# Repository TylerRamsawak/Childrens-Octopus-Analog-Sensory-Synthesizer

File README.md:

# Children's Octopus-themed Analog Sensory Synthesizer

<h3>Rendered 3D model of the PCB</h3>
<br>
<h3>Schematic of the synth and inputs</h3>

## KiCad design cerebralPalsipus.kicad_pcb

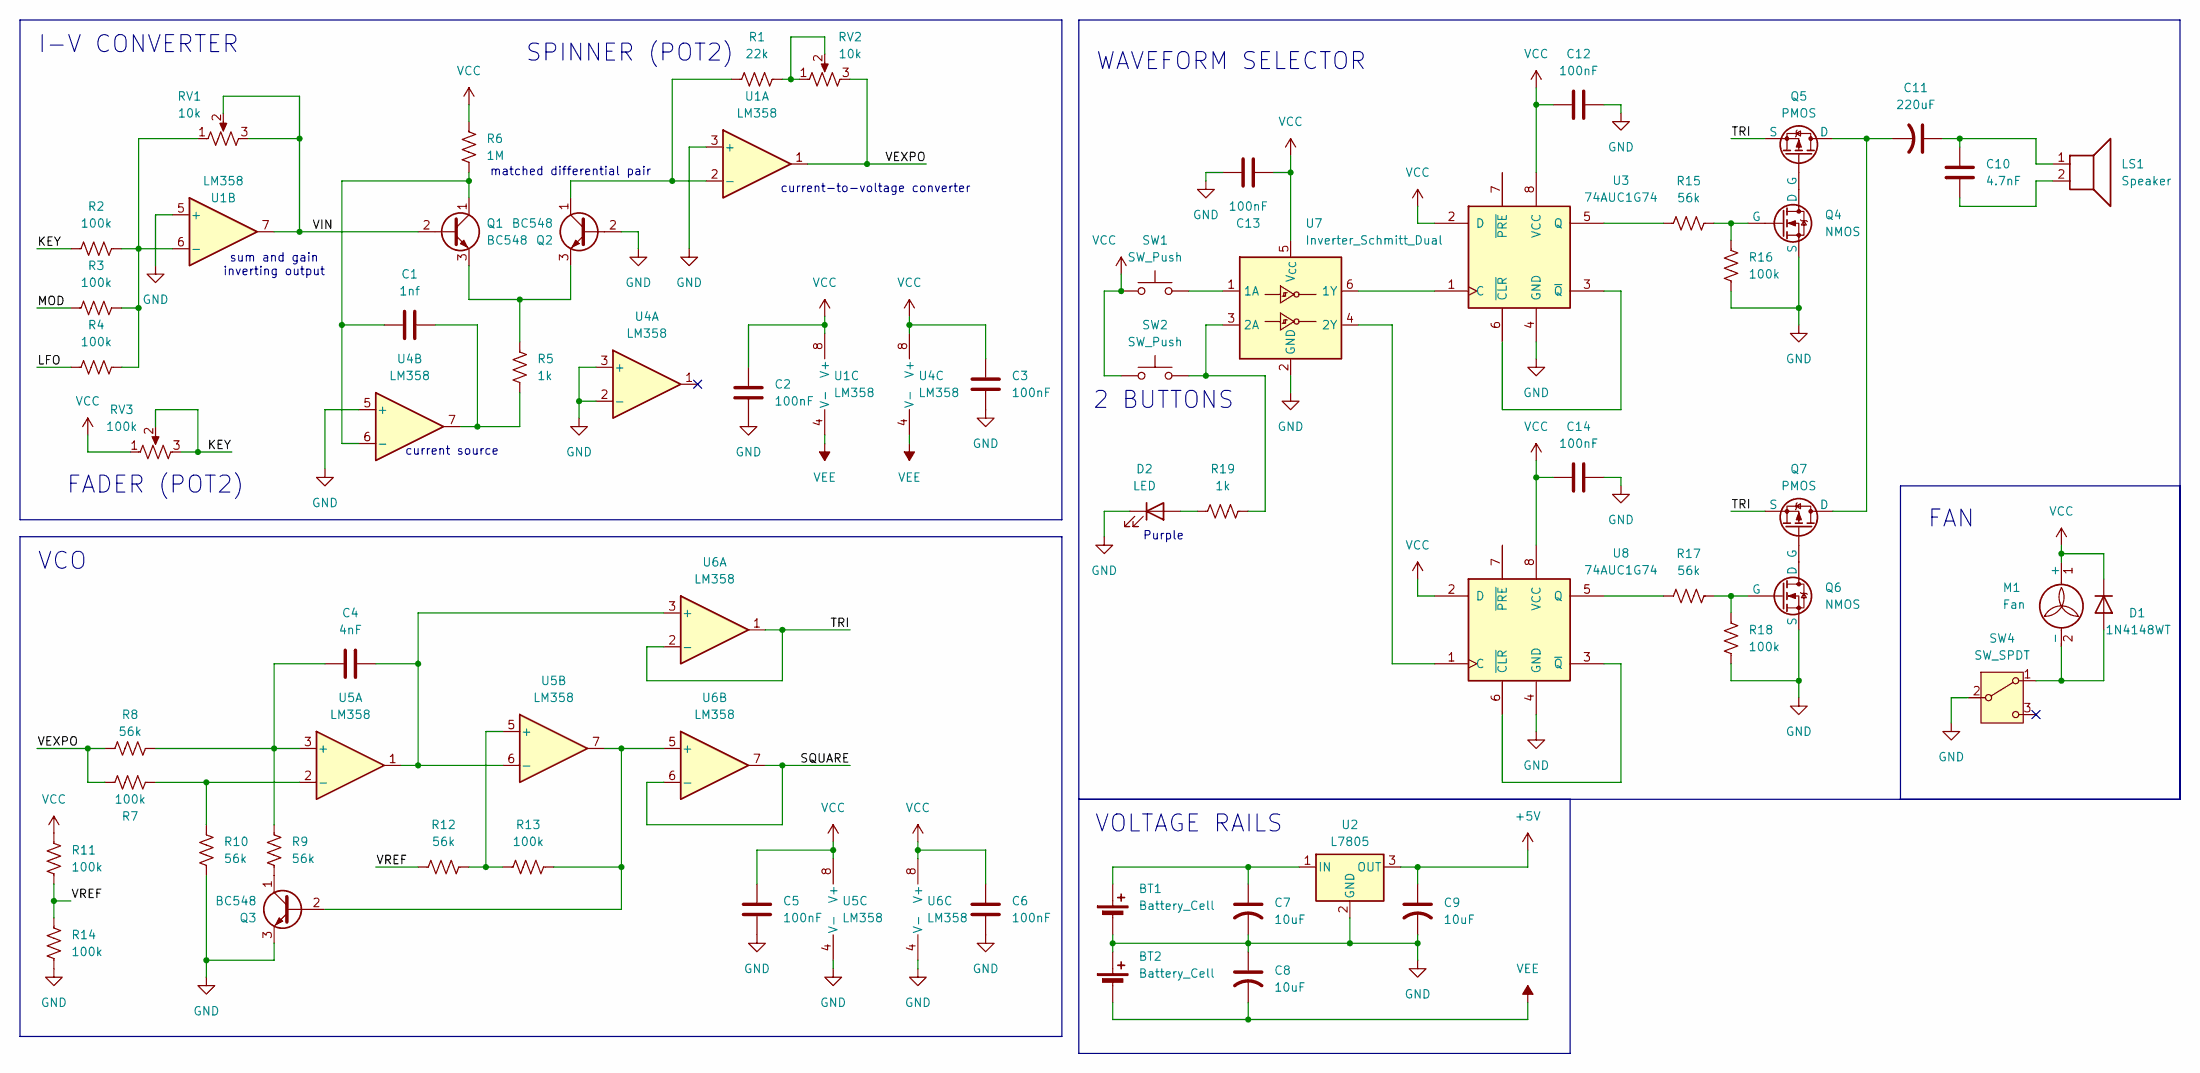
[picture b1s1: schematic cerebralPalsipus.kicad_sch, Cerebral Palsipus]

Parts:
BT1, BT2: Battery_Cell; PinHeader_1x02_P2.54mm_Vertical
C1: 1nf; C_Rect_L4.0mm_W2.5mm_P2.50mm
C2, C3, C5, C6, C12, C13, C14: 100nF; C_Rect_L4.0mm_W2.5mm_P2.50mm
C4: 4nF; C_Rect_L4.0mm_W2.5mm_P2.50mm
C7, C8, C9: 10uF; CP_Radial_D4.0mm_P2.00mm
C10: 4.7nF; C_Rect_L4.0mm_W2.5mm_P2.50mm
C11: 220uF; CP_Radial_D4.0mm_P2.00mm
D1: 1N4148WT; D_SOD-523
D2: LED; PinHeader_1x02_P2.54mm_Vertical
LS1: Speaker; PinHeader_1x02_P2.54mm_Vertical
M1: Fan; PinHeader_1x02_P2.54mm_Vertical
Q1, Q2, Q3: BC548; TO-92_Inline
Q4, Q6: NMOS; TO-92_Inline
Q5, Q7: PMOS; TO-92_Inline
R1: 22k; R_Axial_DIN0204_L3.6mm_D1.6mm_P5.08mm_Horizontal
R2, R3, R4, R7, R11, R13, R14, R16, R18: 100k; R_Axial_DIN0204_L3.6mm_D1.6mm_P5.08mm_Horizontal
R5, R19: 1k; R_Axial_DIN0204_L3.6mm_D1.6mm_P5.08mm_Horizontal
R6: 1M; R_Axial_DIN0204_L3.6mm_D1.6mm_P5.08mm_Horizontal
R8, R9, R10, R12, R15, R17: 56k; R_Axial_DIN0204_L3.6mm_D1.6mm_P5.08mm_Horizontal
RV1, RV2: 10k; PinHeader_1x03_P2.54mm_Vertical
RV3: 100k; PinHeader_1x03_P2.54mm_Vertical
SW1, SW2: SW_Push; PinHeader_1x02_P2.54mm_Vertical
SW4: SW_SPDT; PinHeader_1x02_P2.54mm_Vertical
U1, U4, U5, U6: LM358; DIP-8_W7.62mm_Socket
U2: L7805; TO-252-3_TabPin2
U3, U8: 74AUC1G74; DIP-8_W7.62mm_Socket
U7: Inverter_Schmitt_Dual; DIP-6_W7.62mm

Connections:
+5V: C9.1, U2.3 (OUT)
/KEY: R2.1, RV3.2, RV3.3
/LFO: R4.1
/MOD: R3.1
/SQUARE: U6.6 (-), U6.7
/TRI: Q5.3 (S), Q7.3 (S), U6.1, U6.2 (-)
/VEXPO: R7.1, R8.1, RV2.3, U1.1
/VIN: Q1.2 (B), RV1.2, RV1.3, U1.7
/VREF: R11.2, R12.1, R14.1
GND: BT1.2 (-), BT2.1 (+), C2.1, C3.1, C5.1, C6.1, C7.2, C8.1, C9.2, C12.2, C13.2, C14.2, D2.1 (K), Q2.2 (B), Q3.3 (E), Q4.3 (S), Q6.3 (S), R10.2, R14.2, R16.2, R18.2, SW4.2 (B), U1.3 (+), U1.5 (+), U2.2 (GND), U3.4 (GND), U4.2 (-), U4.3 (+), U4.5 (+), U5.4 (V-), U6.4 (V-), U7.2 (GND), U8.4 (GND)
unnamed: BT1.1 (+), C7.1, U2.1 (IN)
unnamed: C1.2, R5.2, U4.7
unnamed: C10.1, LS1.2
unnamed: C10.2, C11.1, LS1.1
unnamed: D1.2 (A), M1.2 (-), SW4.1 (A)
unnamed: D2.2 (A), R19.1
unnamed: C1.1, Q1.1 (C), R6.2, U4.6 (-)
unnamed: Q1.3 (E), Q2.3 (E), R5.1
unnamed: Q2.1 (C), R1.1, U1.2 (-)
unnamed: Q3.2 (B), R13.2, U5.7, U6.5 (+)
unnamed: Q3.1 (C), R9.2
unnamed: Q4.1 (D), Q5.2 (G)
unnamed: Q4.2 (G), R15.2, R16.1
unnamed: C11.2, Q5.1 (D), Q7.1 (D)
unnamed: Q6.1 (D), Q7.2 (G)
unnamed: Q6.2 (G), R17.2, R18.1
unnamed: R1.2, RV2.1, RV2.2
unnamed: R2.2, R3.2, R4.2, RV1.1, U1.6 (-)
unnamed: U3.1 (C), U7.6 (1Y)
unnamed: R15.1, U3.5 (Q)
unnamed: U3.3 (~Q), U3.6 (~CLR)
unnamed: C4.1, R8.2, R9.1, U5.3 (+)
unnamed: R7.2, R10.1, U5.2 (-)
unnamed: R12.2, R13.1, U5.5 (+)
unnamed: C4.2, U5.1, U5.6 (-), U6.3 (+)
unnamed: SW1.2, U7.1 (1A)
unnamed: R19.2, SW2.2, U7.3 (2A)
unnamed: U7.4 (2Y), U8.1 (C)
unnamed: R17.1, U8.5 (Q)
unnamed: U8.3 (~Q), U8.6 (~CLR)
VCC: C2.2, C3.2, C5.2, C6.2, C12.1, C13.1, C14.1, D1.1 (K), M1.1 (+), R6.1, R11.1, RV3.1, SW1.1, SW2.1, U1.8 (V+), U3.2 (D), U3.8 (VCC), U4.8 (V+), U5.8 (V+), U6.8 (V+), U7.5 (V_{CC}), U8.2 (D), U8.8 (VCC)
VEE: BT2.2 (-), C8.2, U1.4 (V-), U4.4 (V-)

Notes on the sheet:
current-to-voltage converter
sum and gain inverting output
SPINNER (POT2)
WAVEFORM SELECTOR
FADER (POT2)
matched differential pair
2 BUTTONS
VOLTAGE RAILS
FAN
current source
Purple
I-V CONVERTER
VCO

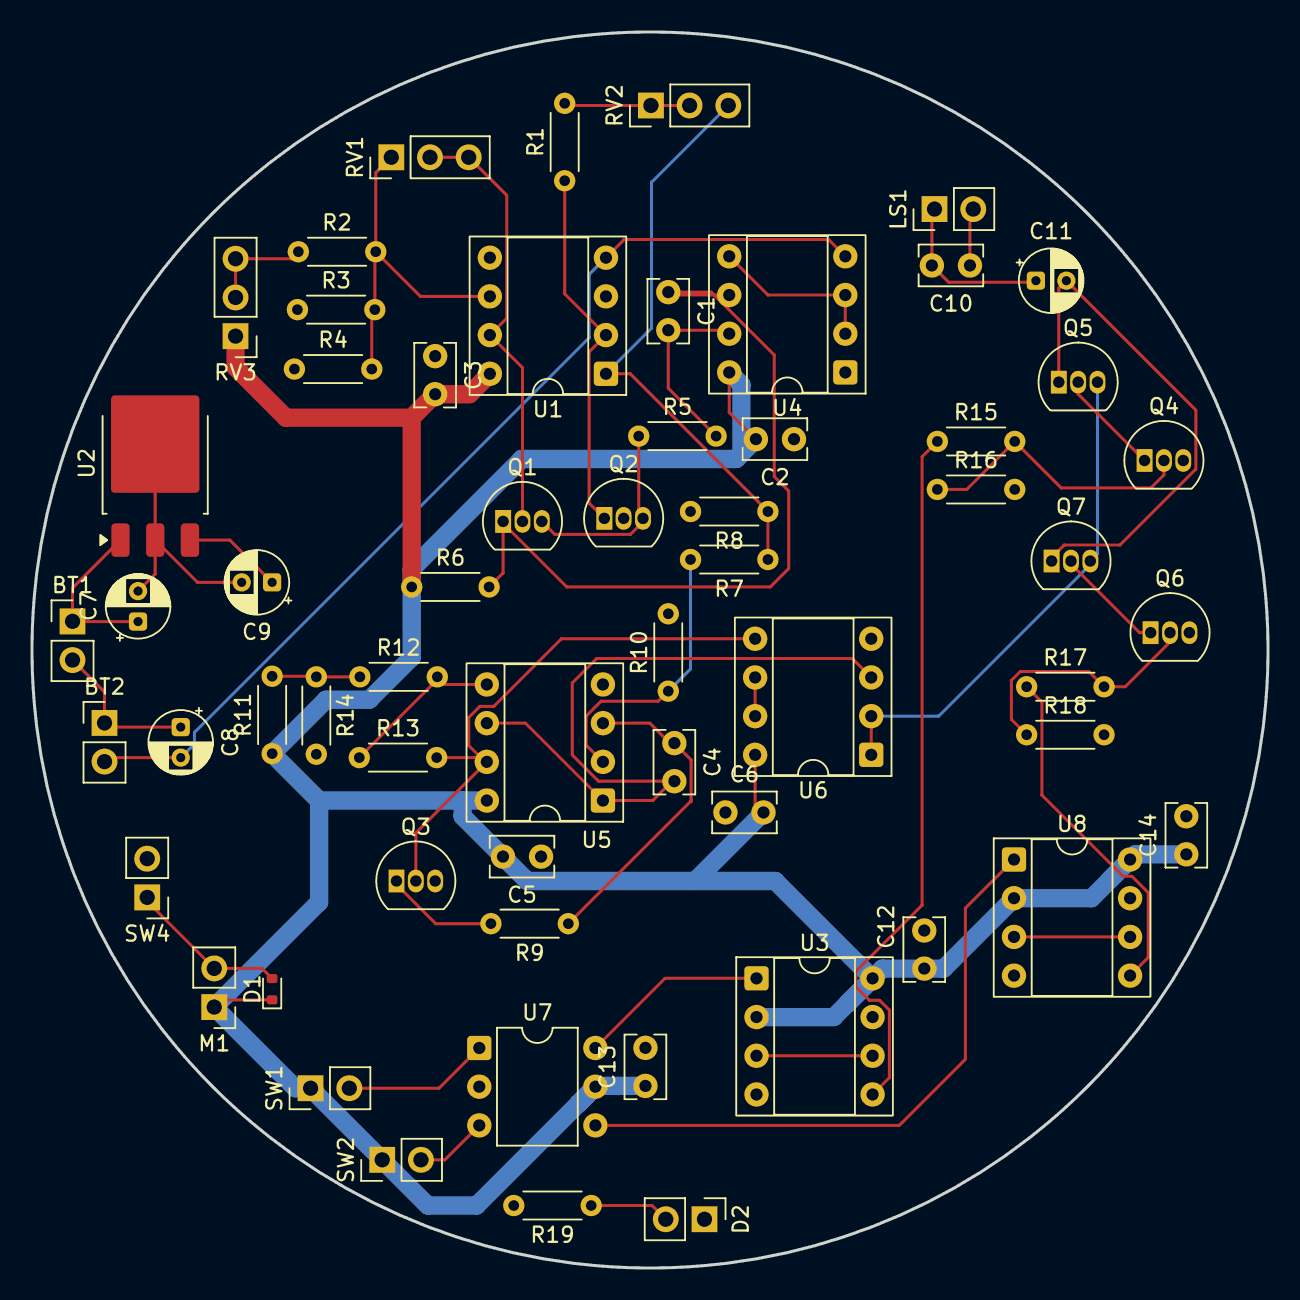
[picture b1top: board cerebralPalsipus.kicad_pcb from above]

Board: 2 copper layers, 81.1 x 81.1 mm, 60 parts (0 on the bottom side), 40 nets.

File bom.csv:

Designator,Footprint,Quantity,Value,LCSC Part #
"BT1, BT2",PinHeader_1x02_P2.54mm_Vertical,2,Battery_Cell,
C1,C_Rect_L4.0mm_W2.5mm_P2.50mm,1,1nf,
C10,C_Rect_L4.0mm_W2.5mm_P2.50mm,1,4.7nF,
C11,CP_Radial_D4.0mm_P2.00mm,1,220uF,
"C12, C13, C14, C2, C3, C5, C6",C_Rect_L4.0mm_W2.5mm_P2.50mm,7,100nF,
C4,C_Rect_L4.0mm_W2.5mm_P2.50mm,1,4nF,
"C7, C8, C9",CP_Radial_D4.0mm_P2.00mm,3,10uF,
D1,D_SOD-523,1,1N4148WT,
D2,PinHeader_1x02_P2.54mm_Vertical,1,LED,
LS1,PinHeader_1x02_P2.54mm_Vertical,1,Speaker,
M1,PinHeader_1x02_P2.54mm_Vertical,1,Fan,
"Q1, Q2, Q3",TO-92_Inline,3,BC548,
"Q4, Q6",TO-92_Inline,2,NMOS,
"Q5, Q7",TO-92_Inline,2,PMOS,
R1,R_Axial_DIN0204_L3.6mm_D1.6mm_P5.08mm_Horizontal,1,22k,
"R10, R12, R15, R17, R8, R9",R_Axial_DIN0204_L3.6mm_D1.6mm_P5.08mm_Horizontal,6,56k,
"R11, R13, R14, R16, R18, R2, R3, R4, R7",R_Axial_DIN0204_L3.6mm_D1.6mm_P5.08mm_Horizontal,9,100k,
"R19, R5",R_Axial_DIN0204_L3.6mm_D1.6mm_P5.08mm_Horizontal,2,1k,
R6,R_Axial_DIN0204_L3.6mm_D1.6mm_P5.08mm_Horizontal,1,1M,
"RV1, RV2",PinHeader_1x03_P2.54mm_Vertical,2,10k,
RV3,PinHeader_1x03_P2.54mm_Vertical,1,100k,
"SW1, SW2",PinHeader_1x02_P2.54mm_Vertical,2,SW_Push,
SW4,PinHeader_1x02_P2.54mm_Vertical,1,SW_SPDT,
"U1, U4, U5, U6",DIP-8_W7.62mm_Socket,4,LM358,
U2,TO-252-3_TabPin2,1,L7805,
"U3, U8",DIP-8_W7.62mm_Socket,2,74AUC1G74,
U7,DIP-6_W7.62mm,1,Inverter_Schmitt_Dual,

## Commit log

2026-02-15 Add README with project overview and images
